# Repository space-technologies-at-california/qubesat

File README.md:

# QubeSat

## PyCubed and OpenLST Repos 
There are several other repositories that can be cloned related to this project:<br/><br/>
PyCubed hardware: https://github.com/pycubed/hardware.git<br/>
PyCubed software: https://github.com/pycubed/software.git<br/>
PyCubed firmware: https://github.com/pycubed/firmware.git<br/>
PyCubed documentation: https://github.com/pycubed/documentation.git<br/><br/>
OpenLST: https://www.planet.com/open/openlst.git<br/>
OpenLST hardware: https://www.planet.com/open/openlst-hw.git<br/>

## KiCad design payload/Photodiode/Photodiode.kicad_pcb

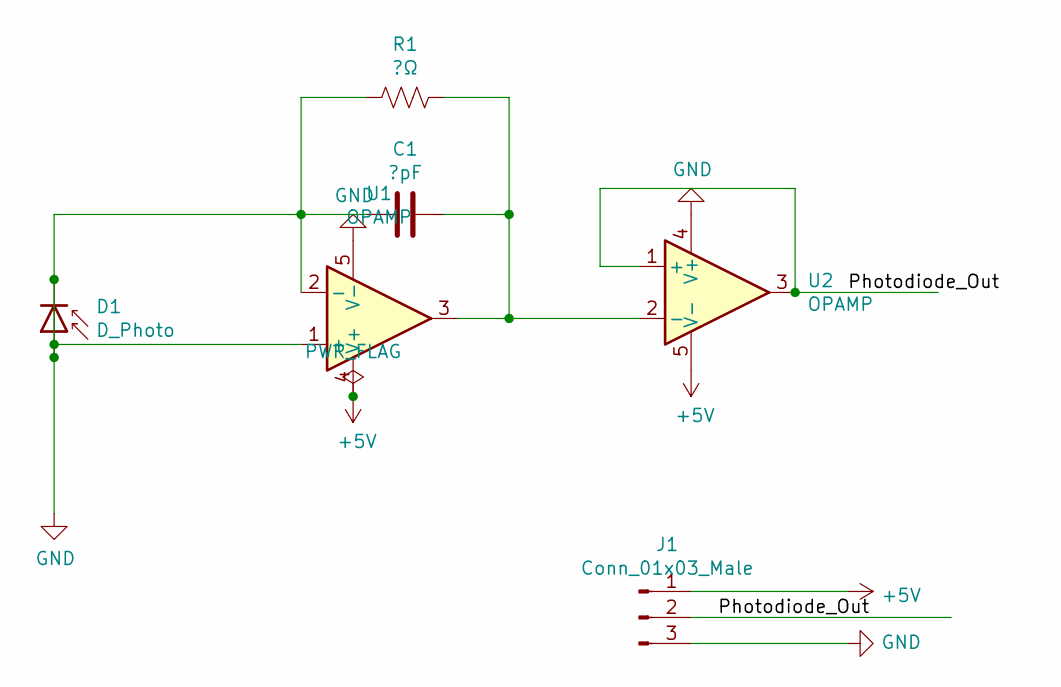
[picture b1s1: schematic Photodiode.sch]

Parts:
C1: ?pF; C_0201_0603Metric
D1: D_Photo; D_0201_0603Metric
J1: Conn_01x03_Male; PinHeader_1x03_P2.54mm_Vertical
R1: ?Ω; R_0201_0603Metric
U1, U2: OPAMP; SOIC-8_3.9x4.9mm_P1.27mm

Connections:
+5V: J1.1, U1.4 (V+), U2.5 (V-)
/Photodiode_Out: J1.2, U2.1 (+), U2.3
GND: C1.2, D1.1 (K), D1.2 (A), J1.3, R1.2, U1.1 (+), U1.2 (-), U1.5 (V-), U2.4 (V+)
unnamed: C1.1, R1.1, U1.3, U2.2 (-)

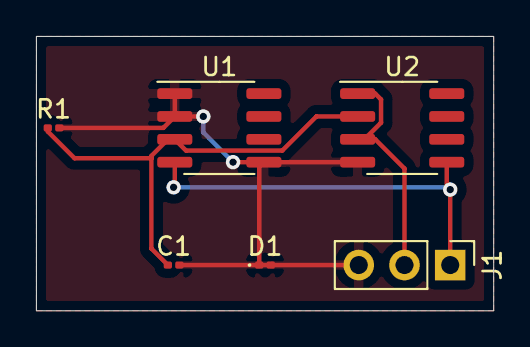
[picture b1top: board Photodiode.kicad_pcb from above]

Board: 2 copper layers, 25.4 x 15.2 mm, 6 parts (0 on the bottom side), 4 nets.

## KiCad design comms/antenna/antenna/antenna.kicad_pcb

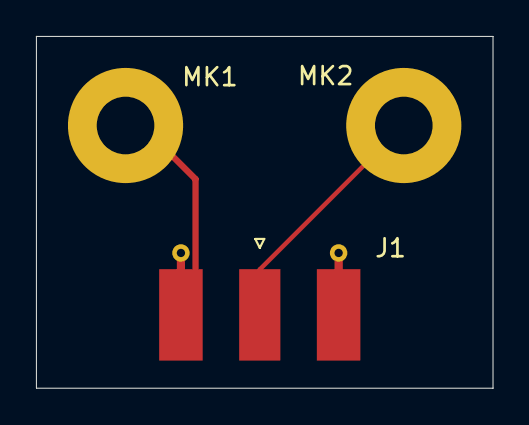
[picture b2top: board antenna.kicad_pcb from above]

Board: 2 copper layers, 25.4 x 19.5 mm, 3 parts (0 on the bottom side), 2 nets.

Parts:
J1: Conn_01x03; SMA_Molex_73251-1153_EdgeMount_Horizontal
MK1, MK2: Mounting_Hole_PAD; MountingHole_3.2mm_M3_Pad

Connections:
unnamed: J1.2, MK2.1
unnamed: J1.3, MK1.1

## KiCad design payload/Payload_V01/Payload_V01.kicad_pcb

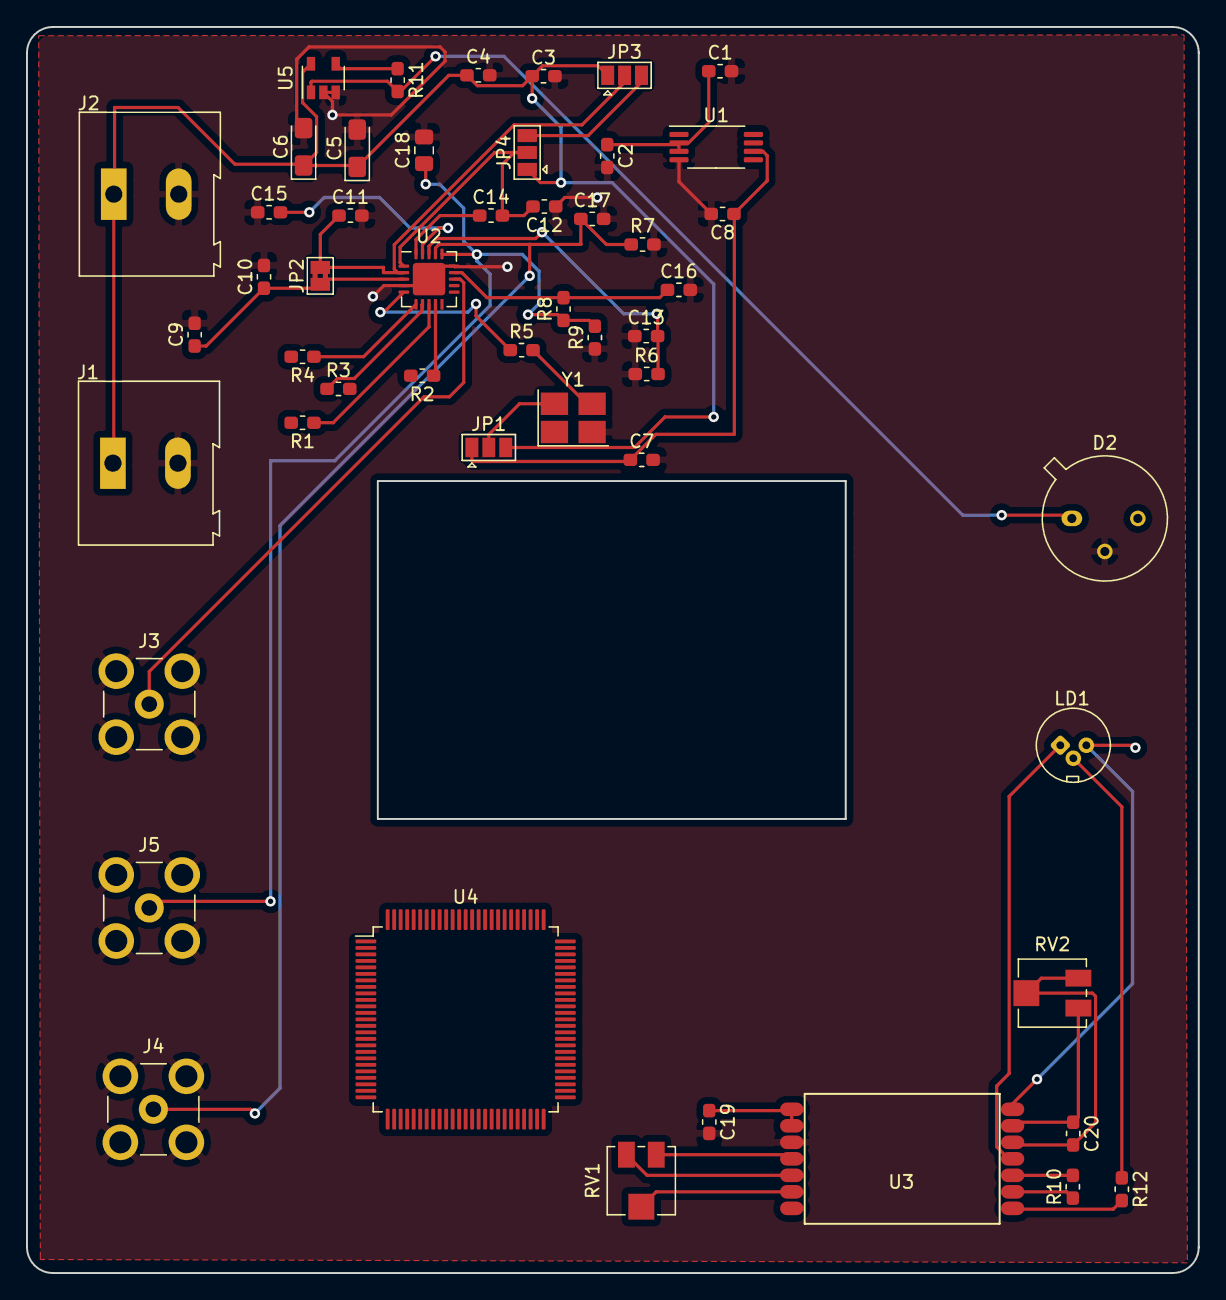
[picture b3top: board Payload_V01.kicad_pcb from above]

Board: 2 copper layers, 90.2 x 95.9 mm, 51 parts (0 on the bottom side), 36 nets.

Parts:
C1, C3, C4, C7, C10, C11, C12, C13, C15, C16, C17: 0.1uF; C_0603_1608Metric_Pad1.05x0.95mm_HandSolder
C2: 10uF; C_0603_1608Metric_Pad1.05x0.95mm_HandSolder
C5, C6: 10uF; CP_EIA-3216-18_Kemet-A_Pad1.58x1.35mm_HandSolder
C8, C9: 1uF; C_0603_1608Metric_Pad1.05x0.95mm_HandSolder
C14: 0.01uF; C_0603_1608Metric_Pad1.05x0.95mm_HandSolder
C18: 0.1uF; C_0805_2012Metric_Pad1.15x1.40mm_HandSolder
C19, C20: C; C_0603_1608Metric_Pad1.05x0.95mm_HandSolder
D2: D_Photo; TO-5-3
J1, J2: Screw_Terminal_01x02; TerminalBlock_Altech_AK300-2_P5.00mm
J3, J4, J5: Conn_Coaxial; SMB_Jack_Vertical
JP1, JP3, JP4: Jumper_3_Open; SolderJumper-3_P1.3mm_Open_Pad1.0x1.5mm
JP2: Jumper; SolderJumper-2_P1.3mm_Bridged2Bar_Pad1.0x1.5mm
LD1: Laserdiode_N_TYPE; LaserDiode_TO18-D5.6-3
R1, R2, R3, R4, R5: 0; R_0603_1608Metric_Pad1.05x0.95mm_HandSolder
R6: 6.8k; R_0603_1608Metric_Pad1.05x0.95mm_HandSolder
R7, R9: 200; R_0603_1608Metric_Pad1.05x0.95mm_HandSolder
R8: 300; R_0603_1608Metric_Pad1.05x0.95mm_HandSolder
R10: 1k; R_0603_1608Metric_Pad1.05x0.95mm_HandSolder
R11, R12: R_US; R_0603_1608Metric_Pad1.05x0.95mm_HandSolder
RV1, RV2: 10k; Potentiometer_Vishay_TS53YJ_Vertical
U1: REF196; TSSOP-8_4.4x3mm_P0.65mm
U2: AD9838; LFCSP-20-1EP_4x4mm_P0.5mm_EP2.5x2.5mm
U3: MLD203P1; MLD203CLN
U4: STM32F407VETx; LQFP-100_14x14mm_P0.5mm
U5: LM321; SOT-23-5
Y1: SG-310SCF; Crystal_SMD_SeikoEpson_TSX3225-4Pin_3.2x2.5mm_HandSoldering

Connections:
+3V3: C3.1, C4.1, C5.1, C6.1, J1.1, J2.1, JP1.3, JP3.1, JP4.1, U5.5
+5V: C19.1, U3.1, U3.2
/Laser/LD_CURR: R10.1, U3.13
/Photodiode/PD_OUT: R11.1, U5.4
/rf_generator/3.3V_BF: JP3.3, JP4.3
/rf_generator/5V_EXT: C1.1, C2.1, U1.2, U1.3
/rf_generator/DVDD1: C11.1, JP2.2, JP3.2, U2.2
GND: C1.2, C2.2, C3.2, C4.2, C5.2, C6.2, C7.2, C8.2, C9.2, C10.2, C11.2, C12.1, C13.1, C15.1, C16.2, C17.2, C18.2, C19.2, D2.2, J1.2, J2.2, J3.2, J4.2, J5.2, R6.1, R7.2, R9.1, U1.4, U2.4, U2.15, U3.3, U5.2, U5.3, Y1.2
unnamed: C7.1, C8.1, JP1.1, U1.6
unnamed: C9.1, C10.1, JP2.1, U2.3
unnamed: C12.2, C14.2, JP4.2, U2.1
unnamed: C13.2, R6.2, U2.18
unnamed: C14.1, U2.20
unnamed: C15.2, U2.19
unnamed: C16.1, R8.2, U2.14
unnamed: C17.1, J4.1, R7.1, U2.17
unnamed: C18.1, J5.1, R8.1, R9.2, U2.16
unnamed: C20.1, RV2.3, U3.9
unnamed: C20.2, RV2.1, RV2.2, U3.10
unnamed: D2.1, R11.2, U5.1
unnamed: J3.1, U2.13
unnamed: JP1.2, Y1.4
unnamed: LD1.1, U3.11
unnamed: LD1.2, R12.1
unnamed: LD1.3, U3.8
unnamed: R1.1, U2.8
unnamed: R2.1, U2.9
unnamed: R3.1, U2.7
unnamed: R4.1, U2.6
unnamed: R5.1, U2.5
unnamed: R5.2, Y1.3
unnamed: R10.2, U3.12
unnamed: R12.2, U3.14
unnamed: RV1.1, U3.5
unnamed: RV1.2, U3.6
unnamed: RV1.3, U3.4

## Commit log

2020-02-09 new files
2020-02-12 Added STACet
2020-02-12 Setting up
2020-02-12 Untracked files issue resolved to fix .gitignore
2020-02-12 Added ideas.txt
2020-02-12 updated ideas.txt
2020-02-19 Updated .gitignore, removed tracking on STACet.iml
2020-02-19 .gitignore is now working
2020-04-12 new pycubed hardware
2020-04-12 deleted
2020-04-12 hardware
2020-04-12 embed
2020-05-27 trying to fix repo
2020-05-27 more delete
2020-05-27 readme
2020-06-29 new pycubed software
2020-06-29 added payload example code
2020-06-29 removed readme
2020-07-20 payload mainboard files
2020-07-20 removed some libraries
2020-07-21 added schematic for rf generator
2020-07-21 updates to schematic
2020-07-22 created new schematic sheets for each part
2020-07-23 added laser and photodiode schematics
2020-08-03 rf generator schematic edit
2020-08-03 something
2020-08-03 initial layout work
2020-08-04 first try importing PCB to solidworks
2020-08-04 added magnets for sizing
2020-08-05 created payload cutout and exported
2020-08-05 tried PCB export
2020-08-05 more mechanical stuff
2020-08-05 something updated
2020-08-05 added footprints and 3d models
2020-08-05 added driver footprint and model
2020-08-05 some changes to schematics
2020-08-06 created photodiode circuit
2020-08-06 fixed op amp footprint
2020-08-06 did some wiring
2020-08-06 tested labels to get microcontroller working
2020-08-06 added some more pins
2020-08-07 fixed laser driver
2020-08-10 small change
2020-10-04 intial antenna PCB
2020-10-04 reorganized to comms folder
2020-10-04 Port Audio + Test program
2020-10-04 Update main.py
    First commit! Created a simple loop that prints the data from all onboard sensors.
2020-10-04 Full duplex out = f(input)
2020-10-09 added flight code demo
2020-10-11 Low pass filter
2020-10-11 Some progress on implementing functions. Thinking of using the finite state machine
2020-10-11 bunch of testing files
2020-10-14 small change to main demo
2020-10-28 Fixed board size
2020-11-02 Implementing save and read functions for SD card
2021-01-05 New structure for ground station. Multiple methods for FSK decoding
2021-01-05 Bug fixes
2021-01-09 payload test code
2021-01-14 payload code V02
2021-01-17 payload code with DMA and interrupts
2021-01-17 initial RF driver code
2021-01-17 Cleaning up metadata folder
2021-01-18 added way to sweep frequency
2021-01-24 V2 RF driver (not working yet)
2021-01-24 Re-wrote the main code from scratch (logic is more clear)
2021-02-07 payload main code + interrupt V01 code
2021-02-14 delay with interrupts intitial commit
2021-02-14 Updated collectPayload() method and integrated SD code into the main code
2021-03-08 new photodiode sch+pcb
2021-03-21 payload code update
2021-07-17 controls code
2021-07-18 Fixed math error, added tests cases
2021-07-18 Bug fixes, quadtratic models, and scale factor
2021-11-12 flight
2021-11-22 Added openlst
